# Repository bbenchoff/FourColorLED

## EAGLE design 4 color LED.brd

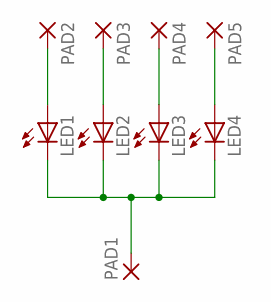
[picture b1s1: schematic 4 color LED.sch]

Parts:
LED1, LED2, LED3, LED4: LEDCHIPLED_0805; CHIPLED_0805
PAD1, PAD2, PAD3, PAD4, PAD5: 1,6/0,8

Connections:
unnamed: LED1.C, LED2.C, LED3.C, LED4.C, PAD1.1
unnamed: LED1.A, PAD2.1
unnamed: LED2.A, PAD3.1
unnamed: LED3.A, PAD4.1
unnamed: LED4.A, PAD5.1

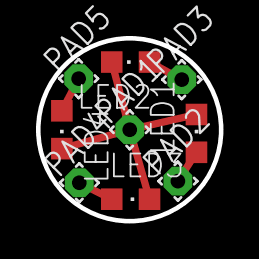
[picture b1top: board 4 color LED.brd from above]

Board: 2 copper layers, 10.2 x 10.2 mm, 9 parts (0 on the bottom side), 5 nets.

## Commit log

2014-01-29 First
    Two boards = one that will be embedded in epoxy for the actual LED, and
    another 'test' board that shows off 10 different frequencies of green.
    Gerbers are good for OSHpark. Included BOM with Mouser part numbers for
    each LED.
